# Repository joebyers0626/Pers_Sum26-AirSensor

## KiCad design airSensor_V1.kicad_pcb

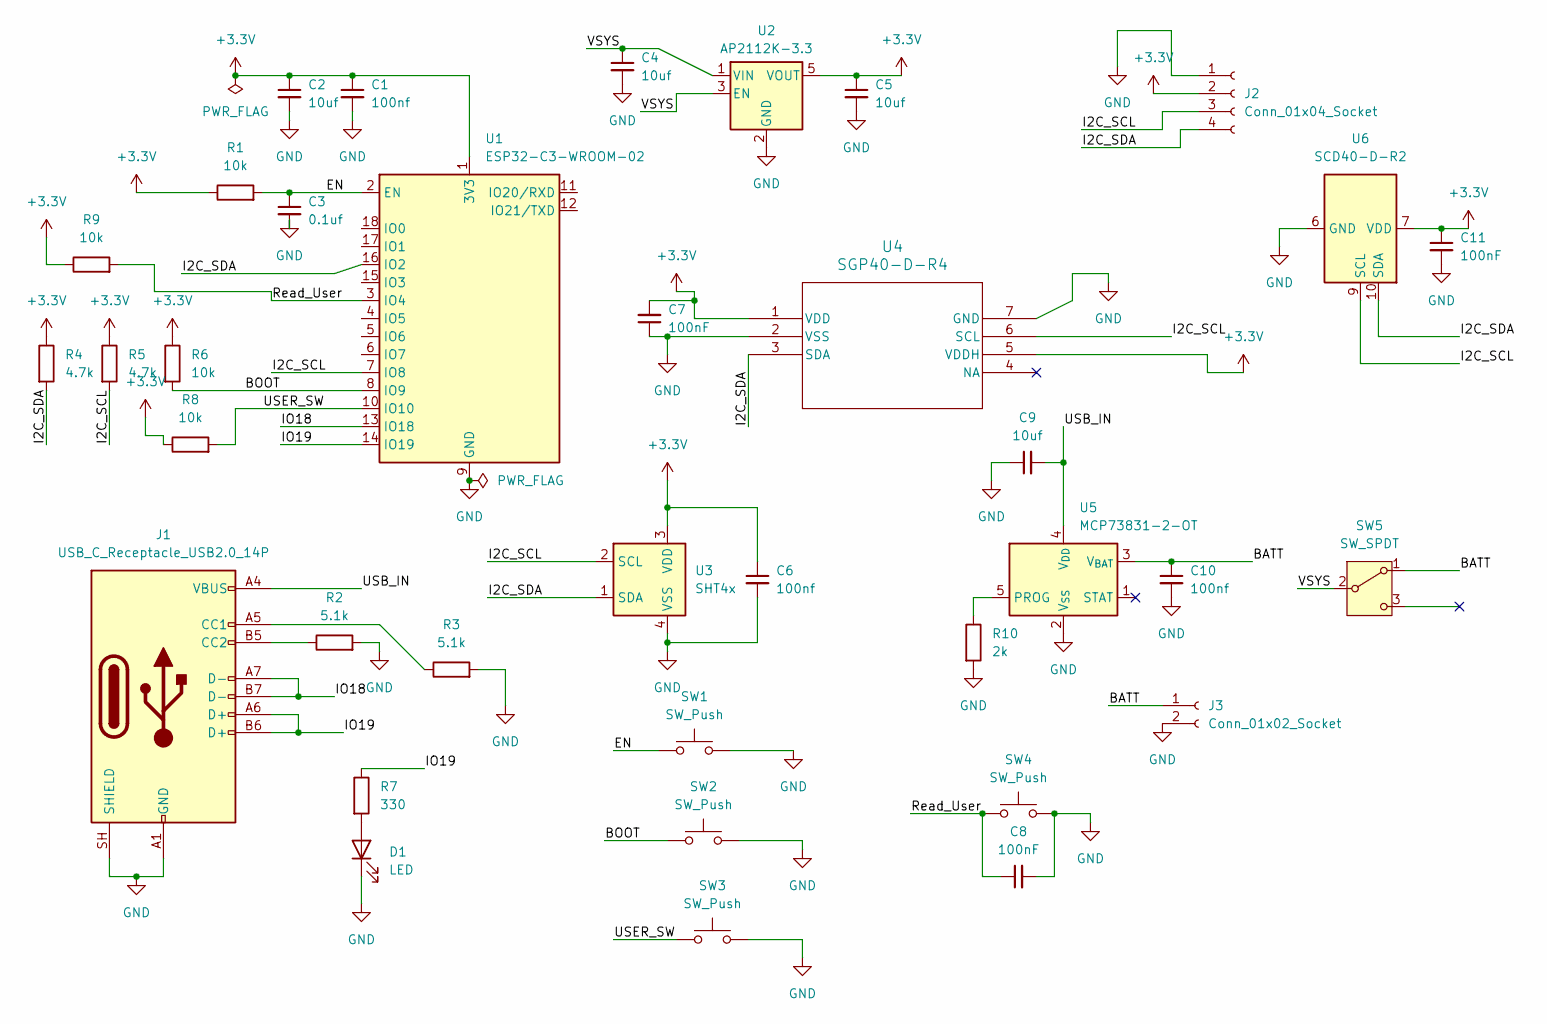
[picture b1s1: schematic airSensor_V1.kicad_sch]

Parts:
C1, C6, C10: 100nf; C_0805_2012Metric
C2, C4, C5, C9: 10uf; C_0805_2012Metric
C3: 0.1uf; C_0805_2012Metric
C7, C8, C11: 100nF; C_0805_2012Metric
D1: LED; LED_0805_2012Metric
J1: USB_C_Receptacle_USB2.0_14P; USB_C_Receptacle_HRO_TYPE-C-31-M-12
J2: Conn_01x04_Socket; PinSocket_1x04_P2.54mm_Vertical
J3: Conn_01x02_Socket; R_0805_2012Metric
R1, R6, R8, R9: 10k; R_0805_2012Metric
R2, R3: 5.1k; R_0805_2012Metric
R4, R5: 4.7k; R_0805_2012Metric
R7: 330; R_0805_2012Metric
R10: 2k; R_0805_2012Metric
SW1, SW2, SW3, SW4: SW_Push; SW_PUSH_6mm
SW5: SW_SPDT; SW_Slide_SPDT_Straight_CK_OS102011MS2Q
U1: ESP32-C3-WROOM-02
U2: AP2112K-3.3; SOT-23-5
U3: SHT4x; Sensirion_DFN-4_1.5x1.5mm_P0.8mm_SHT4x_NoCentralPad
U4: SGP40-D-R4; SGP40_SEN
U5: MCP73831-2-OT; SOT-23-5
U6: SCD40-D-R2; Sensirion_SCD4x-1EP_10.1x10.1mm_P1.25mm_EP4.8x4.8mm

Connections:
+3.3V: C1.1, C2.1, C5.1, C6.1, C7.2, C11.1, J2.2, R1.1, R4.1, R5.1, R6.1, R8.1, R9.1, U1.1 (3V3), U2.5 (VOUT), U3.3 (VDD), U4.1 (VDD), U4.5 (VDDH), U6.7 (VDD), U6.19 (VDD)
/BATT: C10.1, J3.1, SW5.1 (A), U5.3 (V_{BAT})
/BOOT: R6.2, SW2.1, U1.8 (IO9)
/EN: C3.1, R1.2, SW1.1, U1.2 (EN)
/I2C_SCL: J2.3, R5.2, U1.7 (IO8), U3.2 (SCL), U4.6 (SCL), U6.9 (SCL)
/I2C_SDA: J2.4, R4.2, U1.16 (IO2), U3.1 (SDA), U4.3 (SDA), U6.10 (SDA)
/IO18: J1.A7 (D-), J1.B7 (D-), U1.13 (IO18)
/IO19: J1.A6 (D+), J1.B6 (D+), R7.1, U1.14 (IO19)
/Read_User: C8.1, R9.2, SW4.1, U1.3 (IO4)
/USB_IN: C9.2, J1.A4 (VBUS), J1.A9 (VBUS), J1.B4 (VBUS), J1.B9 (VBUS), U5.4 (V_{DD})
/USER_SW: R8.2, SW3.1, U1.10 (IO10)
/VSYS: C4.1, SW5.2 (B), U2.1 (VIN), U2.3 (EN)
GND: C1.2, C2.2, C3.2, C4.2, C5.2, C6.2, C7.1, C8.2, C9.1, C10.2, C11.2, D1.1 (K), J1.A1 (GND), J1.A12 (GND), J1.B1 (GND), J1.B12 (GND), J1.SH (SHIELD), J2.1, J3.2, R2.2, R3.2, R10.2, SW1.2, SW2.2, SW3.2, SW4.2, U1.9 (GND), U1.19 (GND), U2.2 (GND), U3.4 (VSS), U4.2 (VSS), U4.7 (GND), U5.2 (V_{SS}), U6.6 (GND), U6.20 (GND), U6.21 (GND)
unnamed: D1.2 (A), R7.2
unnamed: J1.A5 (CC1), R3.1
unnamed: J1.B5 (CC2), R2.1
unnamed: R10.1, U5.5 (PROG)

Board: 2 copper layers, 36 parts (0 on the bottom side), 17 nets, no tracks yet.

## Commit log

2026-06-04 Initial commit of airSensor project
2026-06-04 Updated air sensor PCB layout
2026-06-04 Saved air sensor layout updates locally
2026-06-09 Initial commit for air sensor project
2026-06-10 Initial commit for air quality sensor
